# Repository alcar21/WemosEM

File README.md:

# WemosEM

:warning::warning::warning: **Sorry, I have no time to work on this project. I am involved in new projects** :warning::warning::warning:

This is a fork of [@nephiel](https://github.com/Nephiel/MQTT-Power-Sensor) and [@Mottramlabs](https://github.com/Mottramlabs/MQTT-Power-Sensor) projects

Thanks to Dawies [www.domology.es](https://domology.es/medidor-de-consumo-no-invasivo-con-sct013-wemos-d1/) for his contributions and his tutorial

The sensor uses a Wemos D1 Mini and PRO and a Non-invasive Split Core Current Transformer type 100A SCT-013-000, available on eBay.
You can use Current Transformer type calibrated SCT-013-030 (30A), SCT-013-050 (50A) and others. Recomended Clamp 30A or higger.

The sensor samples the current value every 10 seconds and publishes it to a topic via an MQTT broker. you can change this value up to 5 seconds
If the connection fails, it attempts to reconnect to the WiFi and/or the MQTT Broker as needed.

Original Gerber files for the PCB layout and the source files for Kicad are included, although there may be issues with the custom libraries used.

**Software features:**

- Easy setup.
- Responsive design.
- Home Asisstant Discovery.
- All setup in web browser: Wifi, MQTT, Calibrate, timezone, update and system.
- Update Voltaje by MQTT topic.
- NTP to setup timezone.
- Blynk Integration
- ThingSpeak integration
- OTA updates
- Optional reset Kwh counter one day of the month
- Reset Kwh in MQTT Topic

#### Components: 
- Wemos D1 Mini / D1 Mini Pro
- [ESP8266 Mains Current Sensor](https://www.ebay.es/itm/ESP8266-Mains-Current-Sensor-Wemos-Current-transformer-SCT013-100A-50mA/133077015640)
- Current transformer SCT013 (Ebay or Aliexpress)
- Optional case: https://www.thingiverse.com/thing:3544702

**WARNING:** If you use calibrated clamp, **REMOVE resistance R1** from mains current sensor.

## Firmware installation and first setup

#### Flashing: 

Download latest [release](https://github.com/alcar21/WemosEM/releases)
You can flash using software [nodemcu-pyflasher](https://github.com/marcelstoer/nodemcu-pyflasher/releases)

1. Select Serial port (COM# port) where your serial-to-USB or NodeMCU/D1 mini is connected. Leave on auto-select if not sure.
2. Browse to the binary you downloaded from WemosEM releases.
3. Set Baud rate to 115200 and **Flash mode to DOUT**. Erase flash to **yes** if it is the first time flashing WemosEM on the device or you're experiencing issues with existing flash. If you're upgrading WemosEM set to no.
4. Click Flash NodeMCU and watch the progress in console.

If the flash was successful the console will display:
  Firmware successfully flashed. unplug/replug or reset device to switch back to normal boot mode

Unplug your adapter or device and plug it back in or connect to another power source. Your device is now ready for Initial configuration.

You can see in Tasmota project other options to flash: https://github.com/arendst/Sonoff-Tasmota/wiki/Flashing

#### Initial configuration

WemosEM provides a wireless access point for easy Wi-Fi configuration.

Connect your device to a power source and grab your smartphone (or tablet or laptop or any other web and Wi-Fi capable device). Search for a Wi-Fi AP named **wemosEM-xxxxxx** (where x is a last part of MAC) and connect to it with password **infinito&masalla**. In this example the Wi-Fi AP is named **wemosEM-AB128A**. When it connects to the network, you may get a warning that there is no Internet connection and be prompted to connect to a different network. Do not allow the mobile device to select a different network.

After you have connected to the WemosEM Wi-Fi AP, open http://192.168.4.1 in a web browser on the smartphone (or whatever device you used). Some devices might prompt you to sign in to Wi-Fi network which should also open the above address.

At this page you can have WemosEM scan for available Wi-Fi networks. Select and setup you wifi network. Click save and you wemos will connect to your wifi.

Finally, connect with IP or http://wemosem-xxxxxx.local/ and enter default user and passwor:

* **Default user: wemosem**
* **Default password: infinito&masalla**

Password is updatable in configuration system tab.

## Ical Value

you can view the ICAL value in http://lechacal.com/wiki/index.php/Current_Transformer_Conditioner

CT | Output Type | Rburden | Rgain (for 5V) | ICAL (for 5V) | Rgain (for 3.3V) | ICAL (for 3.3V)
-- | -- | -- | -- | -- | -- | --
SCT-013-005 | Voltage | None | 130 kΩ | 2.83 | None* | 5.0
SCT-013-010 | Voltage | None | 130 kΩ | 5.66 | None* | 10.0
SCT-013-015 | Voltage | None | 130 kΩ | 8.49 | None* | 15.0
SCT-013-020 | Voltage | None | 130 kΩ | 11.31 | None* | 20.0
SCT-013-025 | Voltage | None | 130 kΩ | 14.14 | None* | 25.0
SCT-013-030 | Voltage | None | 130 kΩ | 16.96 | None* | 30.0
SCT-013-050 | Voltage | None | 130 kΩ | 28.28 | None* | 50.0
SCT-013-060 | Voltage | None | 130 kΩ | 33.94 | None* | 60.0
  |   |   |   |  
SCT-006 | Current | 10 Ω | 17 kΩ | 11.62 | 28 kΩ | 17.5
SCT-013-000 | Current | 10 Ω | 40 kΩ | 56.57 | 75 kΩ | 85.71
SCT-019 | Current | 10 Ω | 24 kΩ | 116.13 | 40 kΩ | 171.43

## Setup in Home Assistant (without MQTT autodiscovery)
    
    sensor:
    - platform: mqtt
      state_topic: "wemos/wemosEM-XXXXXX/power"
      name: WemosEM-Amperaje
      icon: mdi:current-ac
      unit_of_measurement: "A"
      value_template: "{{ value_json.current }}"
    - platform: mqtt
      state_topic: "wemos/wemosEM-XXXXXX/power"
      name: WemosEM-Consumo Actual
      icon: mdi:power-plug
      unit_of_measurement: "W"
      value_template: "{{ value_json.watios }}"
    - platform: mqtt
      state_topic: "wemos/wemosEM-XXXXXX/power"
      name: WemosEM-KWh
      icon: mdi:power-plug
      unit_of_measurement: "KWh"
      value_template: "{{ value_json.kwh }}"nt Cell  | Content Cell  |

## Update Voltaje with Home Assistant

if you have a Shelly EM, add a automation in Home assistant:
      
      - alias: Update voltage WemosEM
        initial_state: 'on'
        trigger:
        - platform: mqtt
          topic: shellies/shellyem-B9E2E9/emeter/0/voltage
    
        action:
        - service: mqtt.publish
          data_template:
            topic: "wemos-cmd/wemosEM-XXXXXX/voltage"
            payload: '{{ trigger.payload }}'

if you have a device with Tasmota, add a automation in Home assistant:

      - alias: Update voltage Tasmota-WemosEM
        initial_state: 'on'
        trigger:
        - platform: mqtt
          topic: tele/sonoff01/SENSOR

        action:
        - service: mqtt.publish
          data_template:
            topic: "wemos-cmd/wemosEM-XXXXXX/voltage"
            payload: "{{ trigger.payload_json['ENERGY'].Voltage }}"

## Blynk Integration

Go to Blynk app on your phone and layout the blynk project with virtual pin number according:
- Virtual PIN V0: Voltage (V)
- Virtual PIN V1: Current (A)
- Virtual PIN V2: Live Watios (w)
- Virtual PIN V3: Energy (kwh)
- Virtual PIN V4: Energy before last reset (kwh)

Setup in web interface token auth, optional you can setup server and port server.

## Thingspeak Integration
Setup in web interface token auth (Write API Key) and Channel number. 
- Field 1: Voltage (V)
- Field 2: Current (A)
- Field 3: Live Watios (w)
- Field 4: Energy (kwh)
- Field 5: Energy before last reset (kwh)

## MQTT Topics
Topic  | Description
------------- | -------------
wemos-cmd/wemosEM-XXXXXX/voltage | Set/update voltage (from sonoff, shelly or other devices)
wemos-cmd/wemosEM-XXXXXX/status | Get Status of wemosEM
wemos-cmd/wemosEM-XXXXXX/resetkwh | reset kwh and store and beforeResetkwh variable

## OTA Updates
OTA updates from platformio windows with espota:
~/.platformio/packages/tool-espotapy/espota.py --progress --ip 192.168.4.1 --auth "infinito&masalla" --file wemosEM-1.3.1_core-2.4.bin

## Developers
This project is developed with **platformio**. WemosEM not compile with core 2.3 because blynk library require core 2.4.0 or higher.
- Recomended compile this project with Arduino Core 2.4.2.

**Commands:**
- Compile: pio run
- Compile and upload Wemos D1: pio run -t upload

Other options:
- Compile with core 2.5: pio run -t upload -e d1_mini_2_5
- Compile for Wemos D1 Mini PRO (**only core 2.4**): pio run -t upload -e d1_mini_pro_2_4

## Tests

## Screenshots

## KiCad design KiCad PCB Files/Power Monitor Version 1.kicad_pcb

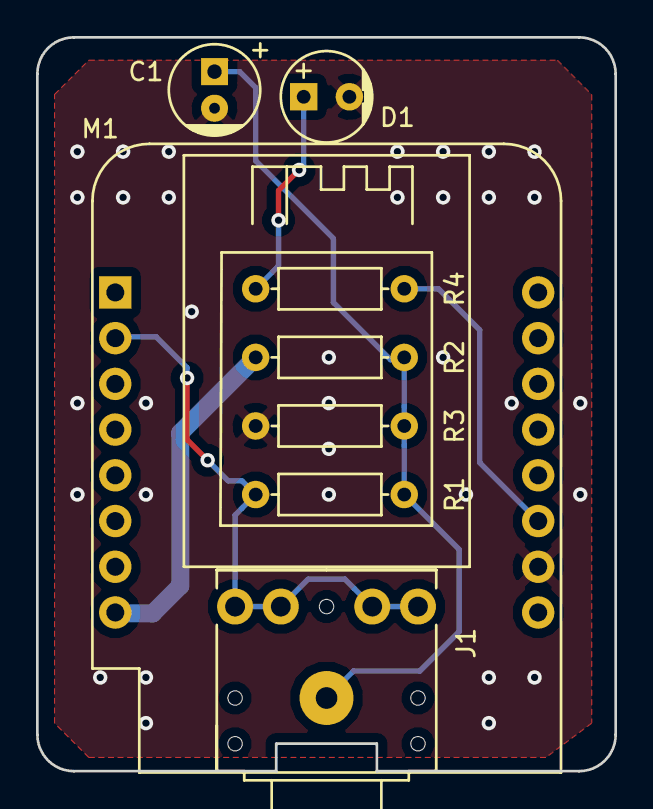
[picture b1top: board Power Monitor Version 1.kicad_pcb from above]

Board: 2 copper layers, 32.1 x 40.8 mm, 8 parts (0 on the bottom side), 6 nets.

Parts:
C1: 10uF 10V; Cap_5mm_THT
D1: LED; LED 5mm
J1: 3.5mm Jack Socket - PJ-307; Jack_3.5_PJ-307
M1: Wemos_D1_Mini; Wemos D1 Mini
R1: 22R; Resistor_THT
R2, R3: 10K; Resistor_THT
R4: 1K; Resistor_THT

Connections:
+3V3: M1.8, R2.1
GND: C1.2, D1.2, M1.10, R3.2
unnamed: C1.1, J1.1, R1.2, R2.2, R3.1
unnamed: D1.1, R4.2
unnamed: J1.2, J1.3, J1.4, J1.5, M1.2, R1.1
unnamed: M1.11, R4.1

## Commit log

2019-09-14 First version
2019-09-14 Fix readme.md
2019-09-14 Re-fix readme.md
2019-09-14 Add Dawies support to readme.md
2019-09-15 improvements documentation readme.md
2019-09-26 Fix wemosem.js to show mqttreconnected change compile params to fix core 2.3.0
2019-10-01 Compress and update fix wemosem.js
2019-10-07 #1 Fixed compiler with arduino 2.3.0
2019-10-09 Create three profiles to compile: - arduino core 2.3 - arduino core 2.4 - arduino core 2.5 Improved web performance
2019-11-04 - Blynk Integration - ThingSpeak integration - Improvement Wifi connection - Optional reset Kwh counter one day of the month - Added parameter with previous kilowatts before reset - Improvement on we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
2019-11-04 - Update documentation
2020-01-22 Working with 2.6.2
2020-01-22 MQTT Enabled Fix
2020-01-24 Playing around
2020-01-29 Day 1
2020-01-31 Day 1 - working
2020-02-01 Day 1.5
2020-02-13 Working
2020-02-14 Temperature
2020-02-15 Gyro only
2020-02-15 Borrowed logic from here
    https://github.com/nkgilley/nodemcu-laundry/blob/master/nodemcu-laundry.
    ino
2020-02-17 CleanUP
2020-02-17 Clean up
2020-02-17 Final
2020-11-01 Fixed #13
